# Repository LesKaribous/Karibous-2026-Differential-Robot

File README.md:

# Karibous-2026-Differential-Robot

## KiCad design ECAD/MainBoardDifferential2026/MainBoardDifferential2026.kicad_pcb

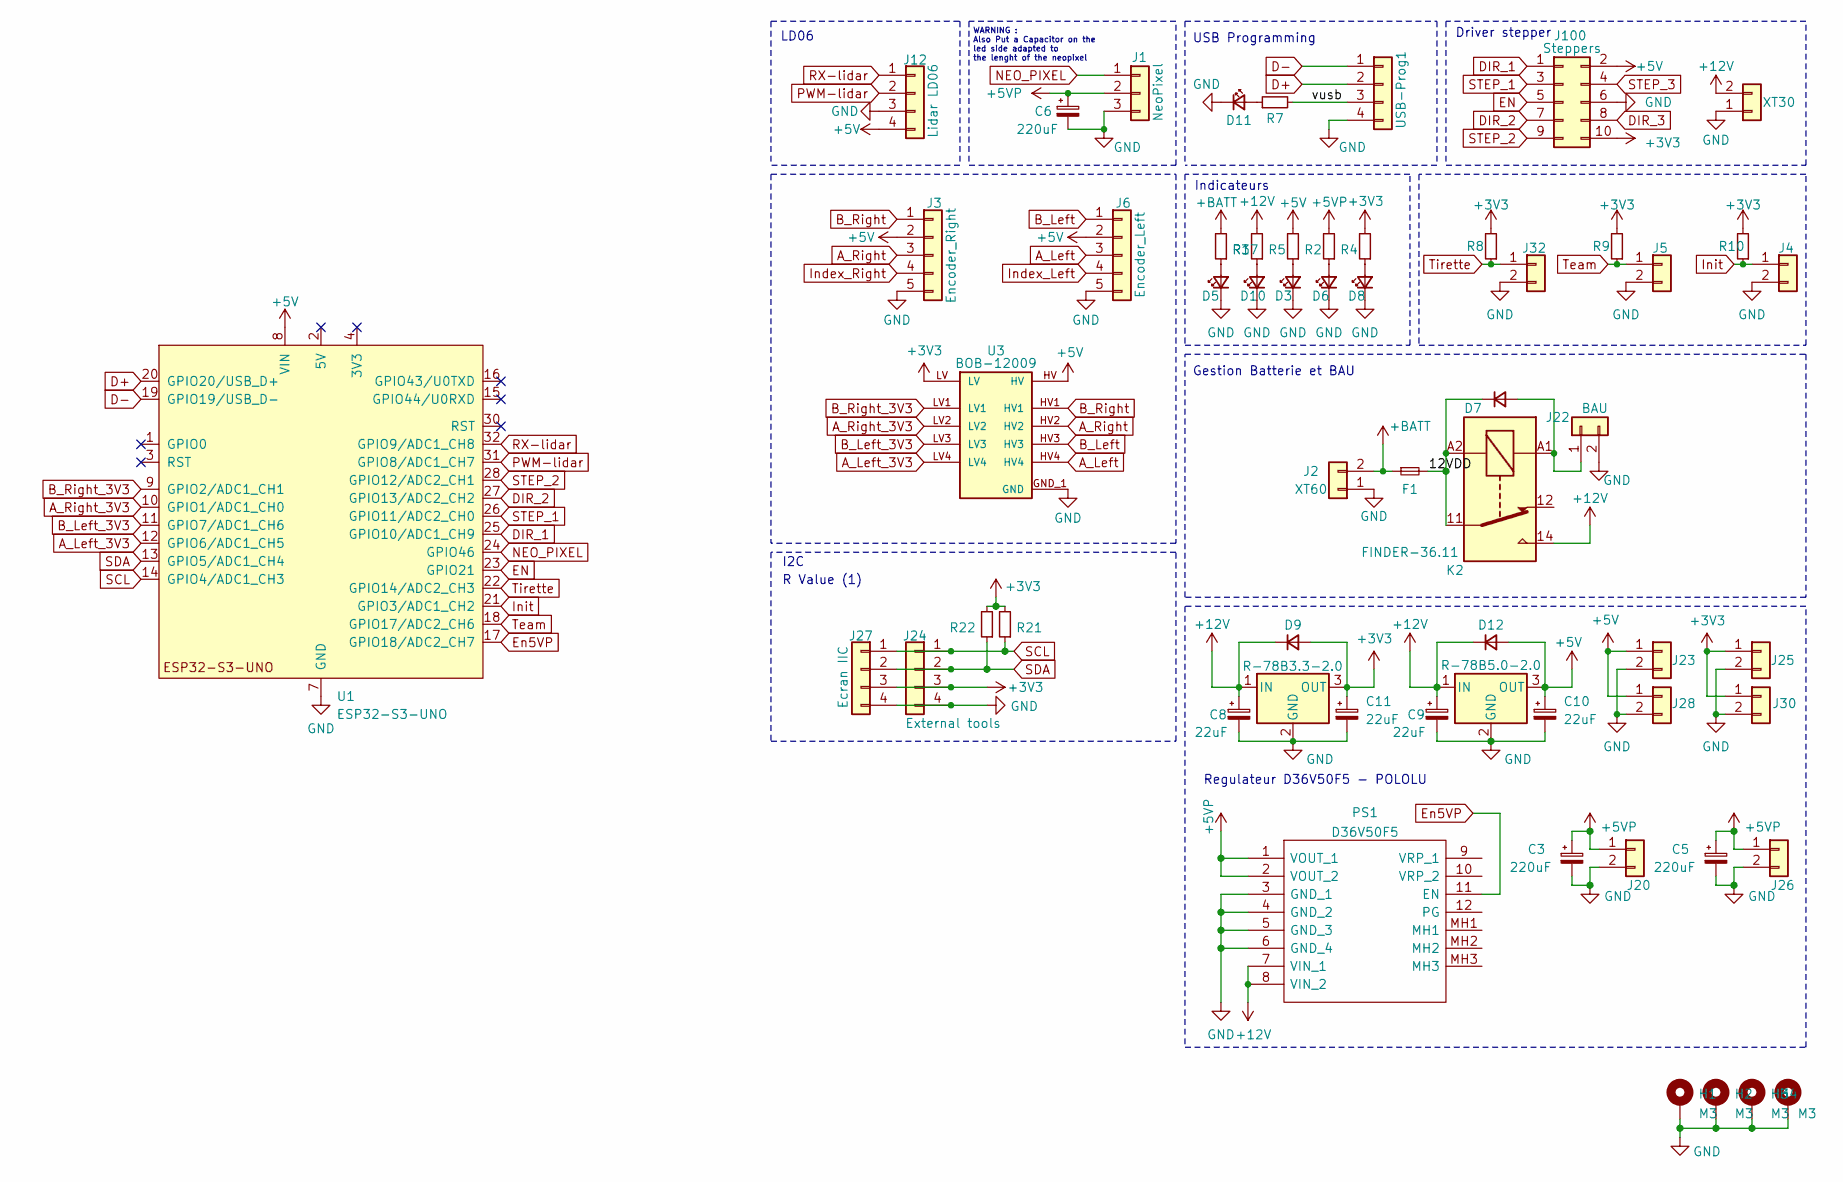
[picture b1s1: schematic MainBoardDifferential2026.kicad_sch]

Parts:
C3, C5, C6: 220uF; CP_Radial_D8.0mm_P3.80mm
C8, C9, C10, C11: 22uF; CP_Elec_5x5.4
D3, D5, D6, D8, D10, D11: LED_Small; LED_1206_3216Metric_Pad1.42x1.75mm_HandSolder
D7, D9, D12: D_Small; D_SMA_Handsoldering
F1: Fuse_Small; Fuseholder_Blade_Mini_Keystone_3568
H1, H2, H3, H4: M3; MountingHole_3.2mm_M3_Pad_Via
J1: NeoPixel; Molex_KK-254_AE-6410-03A_1x03_P2.54mm_Vertical
J2: XT60; AMASS_XT60-M_1x02_P7.20mm_Vertical
J3: Encoder_Right; Molex_KK-254_AE-6410-05A_1x05_P2.54mm_Vertical
J4, J5, J23, J25, J28, J30, J32: Conn_01x02; Molex_KK-254_AE-6410-02A_1x02_P2.54mm_Vertical
J6: Encoder_Left; Molex_KK-254_AE-6410-05A_1x05_P2.54mm_Vertical
J12: Lidar LD06; Molex_KK-254_AE-6410-04A_1x04_P2.54mm_Vertical
J16: XT30; AMASS_XT30U-F_1x02_P5.0mm_Vertical
J20, J22, J26: BAU; Molex_KK-396_A-41791-0002_1x02_P3.96mm_Vertical
J24: External tools; Molex_KK-254_AE-6410-04A_1x04_P2.54mm_Vertical
J27: Ecran IIC; Molex_KK-254_AE-6410-04A_1x04_P2.54mm_Vertical
J100: Steppers; IDC-Header_2x05_P2.54mm_Vertical
K2: FINDER-36.11; Relay_SPDT_Finder_36.11
PS1: D36V50F5; Manufacturer_Part_Number D36V50F5
R2, R3, R4, R5, R7, R17, R21, R22: R_Small; R_1206_3216Metric_Pad1.30x1.75mm_HandSolder
R8, R9, R10: 10k; R_1206_3216Metric_Pad1.30x1.75mm_HandSolder
U1: ESP32-S3-UNO; ESP_S3_UNO
U2: R-78B3.3-2.0; Converter_DCDC_RECOM_R-78B-2.0_THT
U3: BOB-12009; CONV_BOB-12009; PARTREV 01
U5: R-78B5.0-2.0; Converter_DCDC_RECOM_R-78B-2.0_THT
USB-Prog1: Conn_01x04; Molex_KK-254_AE-6410-04A_1x04_P2.54mm_Vertical

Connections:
+3V3: C11.1, D9.2 (A), J24.3, J25.1, J27.3, J30.1, J100.10, R8.2, R9.2, R10.2, R17.2, R21.2, R22.2, U2.3 (OUT), U3.LV
+5V: C10.1, D12.2 (A), J3.2, J6.2, J12.4, J23.1, J28.1, J100.2, R2.2, U1.8 (VIN), U3.HV, U5.3 (OUT)
+5VP: C3.1, C5.1, C6.1, J1.2, J20.1, J26.1, PS1.1 (VOUT_1), PS1.2 (VOUT_2), R4.2
+12V: C8.1, C9.1, D9.1 (K), D12.1 (K), J16.2, K2.14, PS1.7 (VIN_1), PS1.8 (VIN_2), R5.2, U2.1 (IN), U5.1 (IN)
+BATT: F1.1, J2.2, R3.2
/12VDD: D7.1 (K), F1.2, K2.11, K2.A2
/vusb: R7.2, USB-Prog1.3
A_Left: J6.3, U3.HV4
A_Left_3V3: U1.12 (GPIO6/ADC1_CH5), U3.LV4
A_Right: J3.3, U3.HV2
A_Right_3V3: U1.10 (GPIO1/ADC1_CH0), U3.LV2
B_Left: J6.1, U3.HV3
B_Left_3V3: U1.11 (GPIO7/ADC1_CH6), U3.LV3
B_Right: J3.1, U3.HV1
B_Right_3V3: U1.9 (GPIO2/ADC1_CH1), U3.LV1
D+: U1.20 (GPIO20/USB_D+), USB-Prog1.2
D-: U1.19 (GPIO19/USB_D-), USB-Prog1.1
DIR_1: J100.1, U1.25 (GPIO10/ADC1_CH9)
DIR_2: J100.7, U1.27 (GPIO13/ADC2_CH2)
DIR_3: J100.8
EN: J100.5, U1.23 (GPIO21)
En5VP: PS1.11 (EN), U1.17 (GPIO18/ADC2_CH7)
GND: C3.2, C5.2, C6.2, C8.2, C9.2, C10.2, C11.2, D3.1 (K), D5.1 (K), D6.1 (K), D8.1 (K), D10.1 (K), D11.1 (K), H1.1 (1_1), H2.1 (1_1), H3.1 (1_1), H4.1 (1_1), J1.3, J2.1, J3.5, J4.2, J5.2, J6.5, J12.3, J16.1, J20.2, J22.2, J23.2, J24.4, J25.2, J26.2, J27.4, J28.2, J30.2, J32.2, J100.6, PS1.3 (GND_1), PS1.4 (GND_2), PS1.5 (GND_3), PS1.6 (GND_4), U1.6 (GND), U1.7 (GND), U1.29 (GND), U2.2 (GND), U3.GND_1 (GND), U3.GND_2 (GND), U5.2 (GND), USB-Prog1.4
Index_Left: J6.4
Index_Right: J3.4
Init: J4.1, R10.1, U1.21 (GPIO3/ADC1_CH2)
NEO_PIXEL: J1.1, U1.24 (GPIO46)
unnamed: D3.2 (A), R2.1
unnamed: D5.2 (A), R3.1
unnamed: D6.2 (A), R4.1
unnamed: D7.2 (A), J22.1, K2.A1
unnamed: D8.2 (A), R17.1
unnamed: D10.2 (A), R5.1
unnamed: D11.2 (A), R7.1
PWM-lidar: J12.2, U1.31 (GPIO8/ADC1_CH7)
RX-lidar: J12.1, U1.32 (GPIO9/ADC1_CH8)
SCL: J24.1, J27.1, R21.1, U1.14 (GPIO4/ADC1_CH3)
SDA: J24.2, J27.2, R22.1, U1.13 (GPIO5/ADC1_CH4)
STEP_1: J100.3, U1.26 (GPIO11/ADC2_CH0)
STEP_2: J100.9, U1.28 (GPIO12/ADC2_CH1)
STEP_3: J100.4
Team: J5.1, R9.1, U1.18 (GPIO17/ADC2_CH6)
Tirette: J32.1, R8.1, U1.22 (GPIO14/ADC2_CH3)

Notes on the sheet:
I2C
R Value (1)
Driver stepper
USB Programming
LD06
Gestion Batterie et BAU
Regulateur D36V50F5 - POLOLU
Indicateurs
WARNING : Also Put a Capacitor on the led side adapted to the lenght of the neopixel

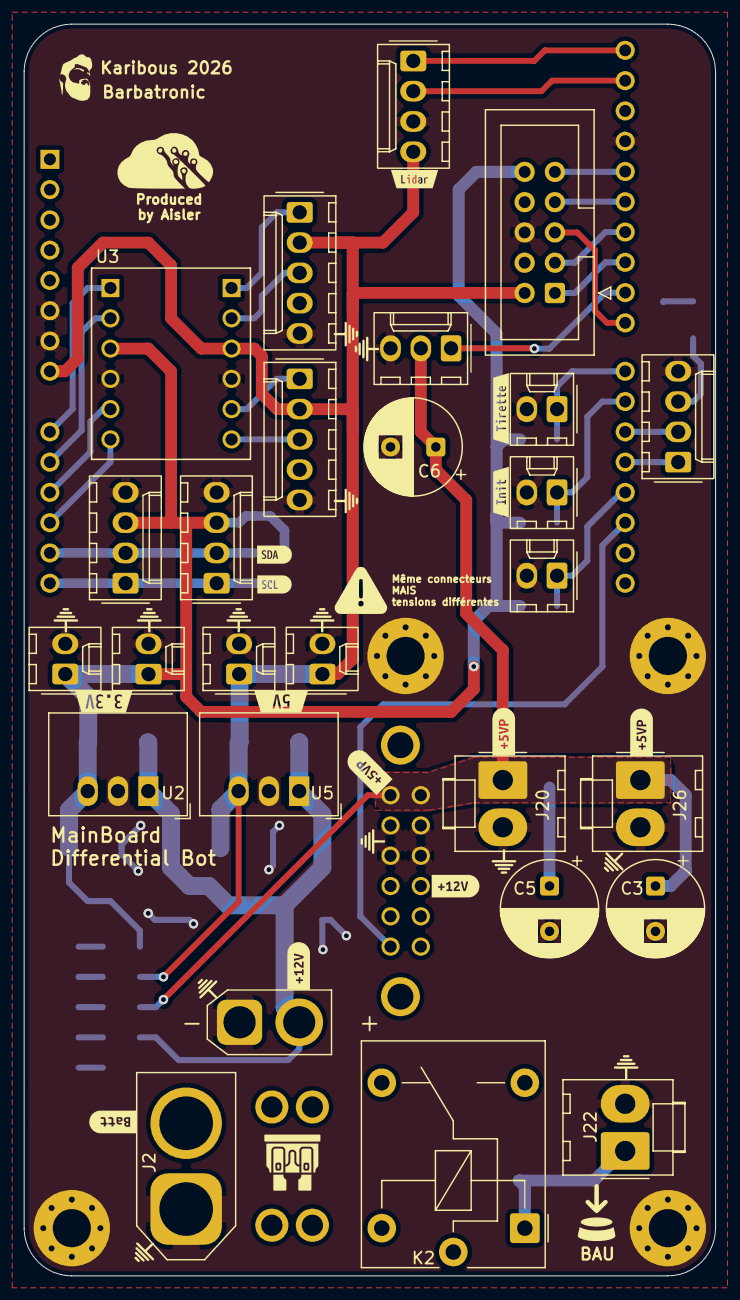
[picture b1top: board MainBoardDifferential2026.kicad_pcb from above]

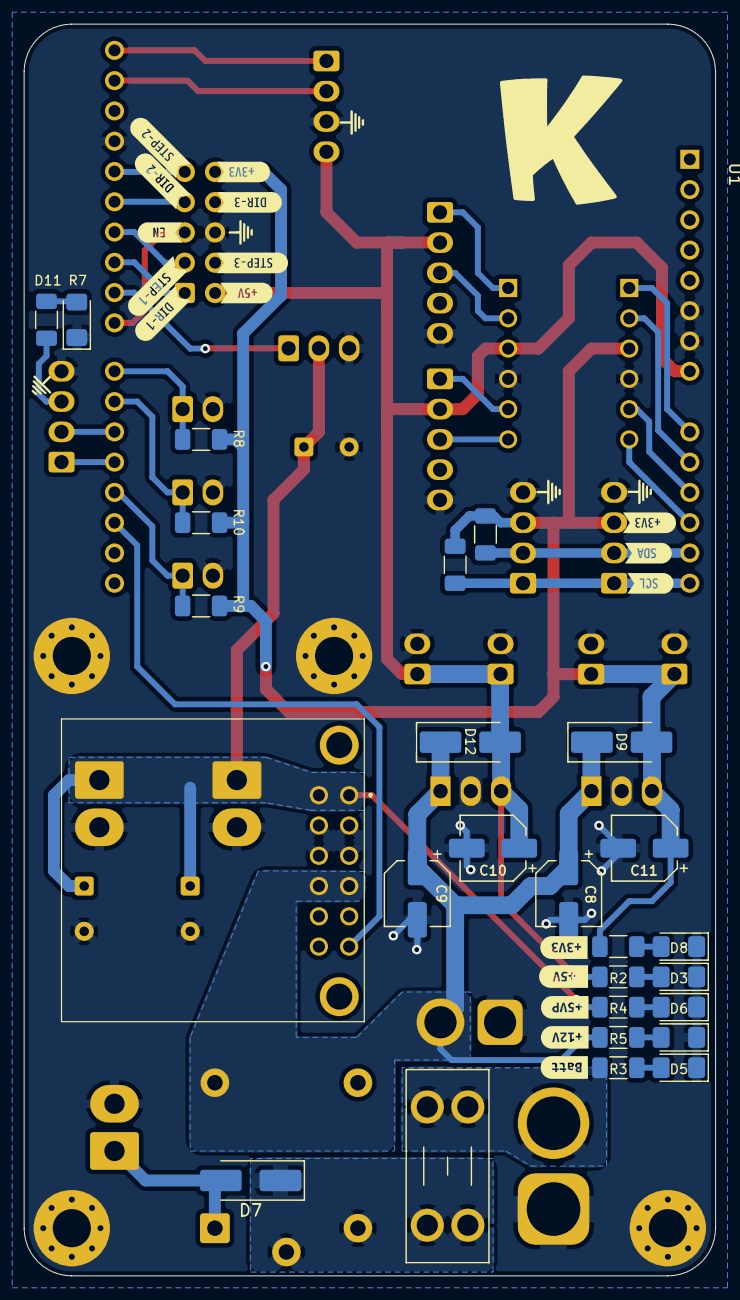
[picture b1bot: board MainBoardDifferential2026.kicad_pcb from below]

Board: 2 copper layers, 58.0 x 105.0 mm, 88 parts (43 on the bottom side), 39 nets.

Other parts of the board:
kibuzzard-670C34D3, kibuzzard-670C34D3#2: G***; kibuzzard-670C34D3
kibuzzard-670C34F5: G***; kibuzzard-670C34F5
kibuzzard-670C38FC: G***; kibuzzard-670C38FC
kibuzzard-670C355C: G***; kibuzzard-670C355C
kibuzzard-670C356A: G***; kibuzzard-670C356A
kibuzzard-670C364B: G***; kibuzzard-670C364B
kibuzzard-670C3331, kibuzzard-670C3331#2: G***; kibuzzard-670C3331
kibuzzard-670C3352, kibuzzard-670C3352#2, kibuzzard-670C3352#3: G***; kibuzzard-670C3352
kibuzzard-670C3359, kibuzzard-670C3359#2, kibuzzard-670C3359#3, kibuzzard-670C3359#4: G***; kibuzzard-670C3359
kibuzzard-670C3379: G***; kibuzzard-670C3379
kibuzzard-670C3380: G***; kibuzzard-670C3380
kibuzzard-670C3554: G***; kibuzzard-670C3554
kibuzzard-670C3560: G***; kibuzzard-670C3560
kibuzzard-670C3565: G***; kibuzzard-670C3565
kibuzzard-670C3571: G***; kibuzzard-670C3571
kibuzzard-670C3577: G***; kibuzzard-670C3577
kibuzzard-670C3646: G***; kibuzzard-670C3646
kibuzzard-670C3872: G***; kibuzzard-670C3872
kibuzzard-670C3904: G***; kibuzzard-670C3904
kibuzzard-6493F0A8: G***; kibuzzard-6493F0A8
kibuzzard-6493F09E: G***; kibuzzard-6493F09E
kibuzzard-64944345: G***; kibuzzard-64944345
kibuzzard-64944398: G***; kibuzzard-64944398

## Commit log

2025-06-20 WIP - First Commit - live 228
2025-06-29 New motorisation and molding wheel
2025-07-05 new molding parts
2025-07-05 Update new mold with hole and larger feet
2025-07-09 add plate and change color
2025-07-11 Semelle et patins lateraux
2025-07-20 Live 232 - Support patin & mat de balise
2025-07-30 Nouveau support batterie
2025-12-22 Update battery support FreeCAD models
2026-02-28 Update connector
2026-04-22 board update
2026-04-22 silkscreen
2026-04-24 Bloc odometrie
2026-04-26 update PAPK 12 2.5 support
2026-04-26 new beacon support and handle
2026-04-26 Live 258
    - Nouveau support d'écran
    - Refonte de la partie IHM
    - Correction du sens de sortie de câble pour la batterie
    - Finalisation des poignées
2026-04-27 add electronics
2026-04-27 update laser parts
2026-04-28 add chamfer
2026-04-29 add laser cutting files
2026-05-03 update carters
2026-05-03 add weight box
2026-05-11 moult modif
